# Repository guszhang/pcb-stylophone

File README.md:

# pcb-stylophone
A simple PCB stylophone for beginners.

## Video
If you have a University of Manchester account, please use the following link to watch the recordings of how I developed this PCB.

[Part 1. Schematic](https://livemanchesterac-my.sharepoint.com/:v:/g/personal/cheng_zhang_manchester_ac_uk/EdEjinE1ZcdDvFBCcBQT6YwBlS-eZUDKp19CB8sIQLojHA?e=sKBfNT)

[Part 2. Layout](https://livemanchesterac-my.sharepoint.com/:v:/g/personal/cheng_zhang_manchester_ac_uk/EXtt0w0fnvxGnB80zMfZI-sBxmpMuy3kb8X-rzs78wH7Fw?e=XIrhHk&nav=eyJyZWZlcnJhbEluZm8iOnsicmVmZXJyYWxBcHAiOiJTdHJlYW1XZWJBcHAiLCJyZWZlcnJhbFZpZXciOiJTaGFyZURpYWxvZyIsInJlZmVycmFsQXBwUGxhdGZvcm0iOiJXZWIiLCJyZWZlcnJhbE1vZGUiOiJ2aWV3In19)

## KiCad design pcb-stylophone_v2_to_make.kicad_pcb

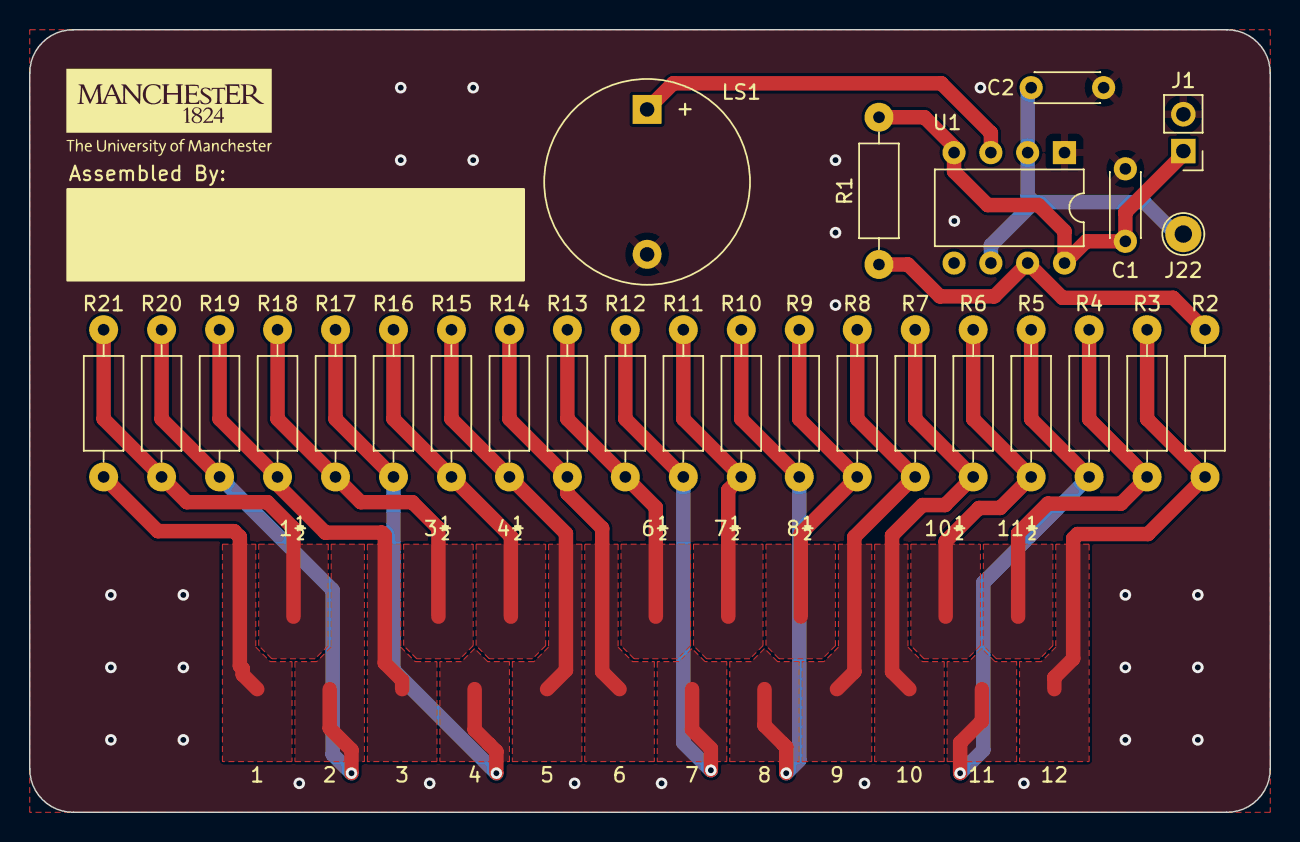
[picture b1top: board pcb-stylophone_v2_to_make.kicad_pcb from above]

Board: 2 copper layers, 85.6 x 54.0 mm, 27 parts (0 on the bottom side), 24 nets.

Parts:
C1: 100n; C_Disc_D4.3mm_W1.9mm_P5.00mm
C2: 10n; C_Disc_D4.3mm_W1.9mm_P5.00mm
J1: Batt; PinHeader_1x02_P2.54mm_Vertical
J22: Stylus; TestPoint_THTPad_D2.5mm_Drill1.2mm
LS1: Piezo Sounder; Buzzer_D14mm_H7mm_P10mm
R1: 10k; R_Axial_DIN0207_L6.3mm_D2.5mm_P10.16mm_Horizontal
R2: 22.1k, 1%; R_Axial_DIN0207_L6.3mm_D2.5mm_P10.16mm_Horizontal
R3: 1.63k, 1%; R_Axial_DIN0207_L6.3mm_D2.5mm_P10.16mm_Horizontal
R4: 1.74k, 1%; R_Axial_DIN0207_L6.3mm_D2.5mm_P10.16mm_Horizontal
R5: 1.82k, 1%; R_Axial_DIN0207_L6.3mm_D2.5mm_P10.16mm_Horizontal
R6: 1.91k, 1%; R_Axial_DIN0207_L6.3mm_D2.5mm_P10.16mm_Horizontal
R7: 2.05k, 1%; R_Axial_DIN0207_L6.3mm_D2.5mm_P10.16mm_Horizontal
R8: 2.15k, 1%; R_Axial_DIN0207_L6.3mm_D2.5mm_P10.16mm_Horizontal
R9: 2.32k, 1%; R_Axial_DIN0207_L6.3mm_D2.5mm_P10.16mm_Horizontal
R10: 2.43k, 1%; R_Axial_DIN0207_L6.3mm_D2.5mm_P10.16mm_Horizontal
R11: 2.61k, 1%; R_Axial_DIN0207_L6.3mm_D2.5mm_P10.16mm_Horizontal
R12: 2.74k, 1%; R_Axial_DIN0207_L6.3mm_D2.5mm_P10.16mm_Horizontal
R13: 2.87k, 1%; R_Axial_DIN0207_L6.3mm_D2.5mm_P10.16mm_Horizontal
R14: 3.01k, 1%; R_Axial_DIN0207_L6.3mm_D2.5mm_P10.16mm_Horizontal
R15: 3.24k, 1%; R_Axial_DIN0207_L6.3mm_D2.5mm_P10.16mm_Horizontal
R16: 3.48k, 1%; R_Axial_DIN0207_L6.3mm_D2.5mm_P10.16mm_Horizontal
R17: 3.65k, 1%; R_Axial_DIN0207_L6.3mm_D2.5mm_P10.16mm_Horizontal
R18: 3.83k, 1%; R_Axial_DIN0207_L6.3mm_D2.5mm_P10.16mm_Horizontal
R19: 4.12k, 1%; R_Axial_DIN0207_L6.3mm_D2.5mm_P10.16mm_Horizontal
R20: 4.32k, 1%; R_Axial_DIN0207_L6.3mm_D2.5mm_P10.16mm_Horizontal
R21: 4.64k, 1%; R_Axial_DIN0207_L6.3mm_D2.5mm_P10.16mm_Horizontal
U1: NE555P; DIP-8_W7.62mm

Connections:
GND: C1.2, C2.2, J1.2, LS1.2, U1.1 (GND)
unnamed: R2.2, R3.1
unnamed: R3.2, R4.1
unnamed: R4.2, R5.1
unnamed: R5.2, R6.1
unnamed: R6.2, R7.1
unnamed: R7.2, R8.1
unnamed: R8.2, R9.1
unnamed: R9.2, R10.1
unnamed: R10.2, R11.1
unnamed: R11.2, R12.1
unnamed: R12.2, R13.1
unnamed: R13.2, R14.1
unnamed: R14.2, R15.1
unnamed: R15.2, R16.1
unnamed: R16.2, R17.1
unnamed: R17.2, R18.1
unnamed: R18.2, R19.1
unnamed: R19.2, R20.1
unnamed: R20.2, R21.1
unnamed: C2.1, J22.1, U1.2 (TR), U1.6 (THR)
unnamed: R1.1, R2.1, U1.7 (DIS)
unnamed: LS1.1, U1.3 (Q)
VCC: C1.1, J1.1, R1.2, U1.4 (R), U1.8 (VCC)

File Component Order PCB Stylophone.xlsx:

Part | Value | Package_DIP:DIP-8_W7.62mm | RS order number | Farnell order code | Note
C1 | 100n | Capacitor_THT:C_Disc_D4.3mm_W1.9mm_P5.00mm | 181-6495
C2 | 10n | Capacitor_THT:C_Disc_D4.3mm_W1.9mm_P5.00mm | 150-3972 |  | 0.05
J1 | Batt | Connector_PinHeader_2.54mm:PinHeader_1x02_P2.54mm_Vertical |  | 3126615 | AAA x4 with switch
LS1 | Piezo Sounder | Buzzer_Beeper:Buzzer_D14mm_H7mm_P10mm | 134-7298
R1 | 10k | Resistor_THT:R_Axial_DIN0207_L6.3mm_D2.5mm_P7.62mm_Horizontal |  | 3496944 | 0.01
R2 | 22.1k, 1% | Resistor_THT:R_Axial_DIN0207_L6.3mm_D2.5mm_P7.62mm_Horizontal |  | 3541246 | 0.01
R3 | 1.62k, 1% | Resistor_THT:R_Axial_DIN0207_L6.3mm_D2.5mm_P7.62mm_Horizontal |  | 3541183 | 0.01
R4 | 1.74k, 1% | Resistor_THT:R_Axial_DIN0207_L6.3mm_D2.5mm_P7.62mm_Horizontal |  | 3541196 | 0.01
R5 | 1.82k, 1% | Resistor_THT:R_Axial_DIN0207_L6.3mm_D2.5mm_P7.62mm_Horizontal |  | 3952882 | 0.01
R6 | 1.91k, 1% | Resistor_THT:R_Axial_DIN0207_L6.3mm_D2.5mm_P7.62mm_Horizontal |  | 9465472 | 0.01
R7 | 2.05k, 1% | Resistor_THT:R_Axial_DIN0207_L6.3mm_D2.5mm_P7.62mm_Horizontal |  | 3541227 | 0.01
R8 | 2.15k, 1% | Resistor_THT:R_Axial_DIN0207_L6.3mm_D2.5mm_P7.62mm_Horizontal |  | 9466703 | 0.01
R9 | 2.32k, 1% | Resistor_THT:R_Axial_DIN0207_L6.3mm_D2.5mm_P7.62mm_Horizontal |  | 3541254 | 0.01
R10 | 2.43k, 1% | Resistor_THT:R_Axial_DIN0207_L6.3mm_D2.5mm_P7.62mm_Horizontal |  | 3541263 | 0.01
R11 | 2.61k, 1% | Resistor_THT:R_Axial_DIN0207_L6.3mm_D2.5mm_P7.62mm_Horizontal |  | 3541275 | 0.01
R12 | 2.74k, 1% | Resistor_THT:R_Axial_DIN0207_L6.3mm_D2.5mm_P7.62mm_Horizontal |  | 3541013 | 0.01
R13 | 2.87k, 1% | Resistor_THT:R_Axial_DIN0207_L6.3mm_D2.5mm_P7.62mm_Horizontal |  | 9466851 | 0.01
R14 | 3.01k, 1% | Resistor_THT:R_Axial_DIN0207_L6.3mm_D2.5mm_P7.62mm_Horizontal |  | 3975196 | 0.01
R15 | 3.24k, 1% | Resistor_THT:R_Axial_DIN0207_L6.3mm_D2.5mm_P7.62mm_Horizontal |  | 9467807 | 0.01
R16 | 3.48k, 1% | Resistor_THT:R_Axial_DIN0207_L6.3mm_D2.5mm_P7.62mm_Horizontal |  | 3541342 | 0.01
R17 | 3.65k, 1% | Resistor_THT:R_Axial_DIN0207_L6.3mm_D2.5mm_P7.62mm_Horizontal |  | 3541352 | 0.01
R18 | 3.83k, 1% | Resistor_THT:R_Axial_DIN0207_L6.3mm_D2.5mm_P7.62mm_Horizontal |  | 9467904 | 0.01
R19 | 4.12k, 1% | Resistor_THT:R_Axial_DIN0207_L6.3mm_D2.5mm_P7.62mm_Horizontal |  | 9468625 | 0.01
R20 | 4.32k, 1% | Resistor_THT:R_Axial_DIN0207_L6.3mm_D2.5mm_P7.62mm_Horizontal |  | 9468650 | 0.01
R21 | 4.64k, 1% | Resistor_THT:R_Axial_DIN0207_L6.3mm_D2.5mm_P7.62mm_Horizontal |  | 9468684 | 0.01
U1 | NE555P | Package_DIP:DIP-8_W7.62mm | 866-0199 |  | already ordered

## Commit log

2023-05-18 calculations of resistors and capacitors
2023-05-19 finalised v1
2023-05-19 additional sync
2023-07-28 stylophone v2 has bigger resistor soldering pads
2023-08-10 added v2 gerber files
